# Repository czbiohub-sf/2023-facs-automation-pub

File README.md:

# FACSAutomation

## Introduction
This repository contains the Python application and custom **czfacsautomation** package that have been designed for automating the cell sorting on the Sony SH800S, by the CZ Biohub - SF Bioengineering team. All utilities support Python 3.7. Note that newer versions of Python are not compatible.

*This is a public snapshot of the FACS Automation repo as described in our 2023 preprint [here](https://www.biorxiv.org/content/10.1101/2023.03.24.534165v1).*

Maintenance of this repo is the responsibility of Diane Wiener. Please direct any communication to Diane Wiener via creation of an Issue at the project repo [here](https://github.com/czbiohub/2023-facs-automation-pub/issues).

This source describes Open Hardware, which is licensed under the CERN-OHL-W v2. 

Electronics hardware is described in the facs_electronics folder.

CAD designs are provided in Onshape [here](https://cad.onshape.com/documents/c1a3ab256e8df7a71b82db8c/w/ab65c37920d47d4a2484a277/e/421207c6e308bccf3dd4e5b1?configuration=default&renderMode=0&uiState=640b930bf24bcf207edf60a6).

Software is licensed under BSD 3-Clause.

Copyright Chan Zuckerberg Biohub - San Francisco 2023.

## Contents

### Classes
`czfacsautomation/hardware/`
* __`HardwareController`__ - Interfaces with hardware peripherals
* __`ZaberController`__ - Communicates with the zaber stages and gripper
* __`ArduinoController`__ - Communicates with the arduino via serial

`czfacsautomation/sorting/`
* __`Controller`__ - Creates wrapper classes for auto click methods used for interfacing with the Sony SH800S GUI
* __`Sort`__ - Runs a single sort on the Sony SH800S GUI
* __`Gating`__ - Runs the GateVertexTool to get and set gate on the Sony SH800S GUI
* __`CreateGate`__ - Creates a custom gate using the cell population data

`czfacsautomation/integration/`
* __`FACSAutomation`__ - Main class to call, starts process, and implements pause/stop

`czfacsautomation/slack/`
* __`SlackFacs`__ - Communicates with Slack App to notify users of current run status.

### Config Files
* __`config/hardware_config.json`__ - Holds the hardware configuration parameters for the zaber stages and arduino
* __`config/gui_config.json`__ - Holds the config file of all screenshots and parameters needed to run sorting
* __`config/Slack_config.json`__ - Holds the configuration parameters for the various messages to post

### Vendor Folder
The GateVertexTool `vendor/GateVertexTool.exe` is available from Sony Biotechnology.
Requests to access the GateVertexTool may be made to SONY Biotechnology [here](https://go.sonybiotechnology.com/gate-vertex.html).
Store the file in the `vendor/GateVertexTool/` folder.

## Installation and Use
### Installing Module
1. On Windows OS: Add GateVertexTool folder to "Path" environment variable (read release notes for more details)
2. Create and/or activate a virtual environment in a convenient location with Python3
3. Install and add pytesseract to path
4. Download / clone this repository
5. Navigate to the base of the repository
6. Install setuptools `pip install setuptools`
7. Install module `pip install -e .`
8. Create the folder for the exported gating data in the location specified in the "GATE_CSV_DIR" path in the `gui_config.json` 

### Updating Module from Repository
1. Pull changes from remote repository
2. Activate virtual environment with previous install
3. Navigate to the module directory
4. Update module `pip install -e . --upgrade`

### Using Module
1. cd to the `src` directory
2. `python -m czfacsautomation "<hardware_config location>" "-facs" ""`

#### Module Routines:
1. Chill Tube Housing:
   
   `python -m czfacsautomation "<hardware_config location>" "-chill" ""`

2. Run FACS Automation:
   
   `python -m czfacsautomation "<hardware_config location>" "-facs" ""`

3. Data Scraper:
   
   `python -m czfacsautomation "<hardware_config location>" "-scrape" ""`

4. Hardware Demo:
   
   `python -m czfacsautomation "<hardware_config location>" "-demo" ""`

5. Calibration:
   
   a. Calibration Update Scan:
      
   `python -m czfacsautomation "<hardware_config location>" "-calibrate" "-s"`
   
   b. Tube Calibration Check:
      
   `python -m czfacsautomation "<hardware_config location>" "-calibrate" "-t"`
   
   c. Full Calibration Routine (Scanning and with Tubes):
      
   `python -m czfacsautomation "<hardware_config location>" "-calibrate" "-f"`

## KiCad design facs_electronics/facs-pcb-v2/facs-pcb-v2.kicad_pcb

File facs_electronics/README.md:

# FACSAutomation
Python libraries for automating cell sorting with the Sony SH800S GUI.

# Serial Commands
All commands should be sent via Serial with a newline ending, `\n`, e.g. send `VALVE\n`.
Upon initialization, all 18 motors are initialized but turned off, and the valve is switched open.
| Command | Description |
|--|--|
| `VALVE` | Toggles solenoid valve on/off. Solenoid is normally closed but initialized open. |
|`READ_TEMP` | Upon calling, will average collected temperature readings from 6 sensors and return in a string 0,0,0,0,0,0 |
|`M,X` | Reads motor status, where X is the motor of interest (zero-indexed). Let X = -1 to return all motor statuses in the form 0,0,0,0,0,0,0,0,0,0,0,0,0,0,0,0,0,0.|
|`S,[X]` | Switches state of motors, where X can be a variable list of motor nums (zero-indexed); e.g., `S,[0,1,2,17]` to toggle motor # 0, 1, 2, and 17 or `S,[0]` to toggle just the first motor. Will return `[motor_num, old state, new state]`, e.g. `[5, 1, 0]` if turning off the 5th (0-indexed) motor.|
|`E,X` | Stops motors based on the encoder reading. The motor must be turned on using `S,[X]` before using the encoder. When the encoder successfully picks up a signal, it will return:<br>`Detected`<br> `[motor_num,1,0]`<br>If it is unsuccessful, it will return: <br>`Not detected`<br>`[motor_num,1,0]`|
|`P,X`| Changes PWM of motors to X, ranging from 0-255.|
| `ON`| Turns all 18 motors on and sets PWM to 150.
| `OFF`| Turns all motors off AND sets PWM to 0 (think low-power OFF). To turn back on, either use `P,X` to set PWM and then toggle motors with `S,[X]` to turn on motors; or, `ON` to set PWM to 150 and enable all 18 motors. |

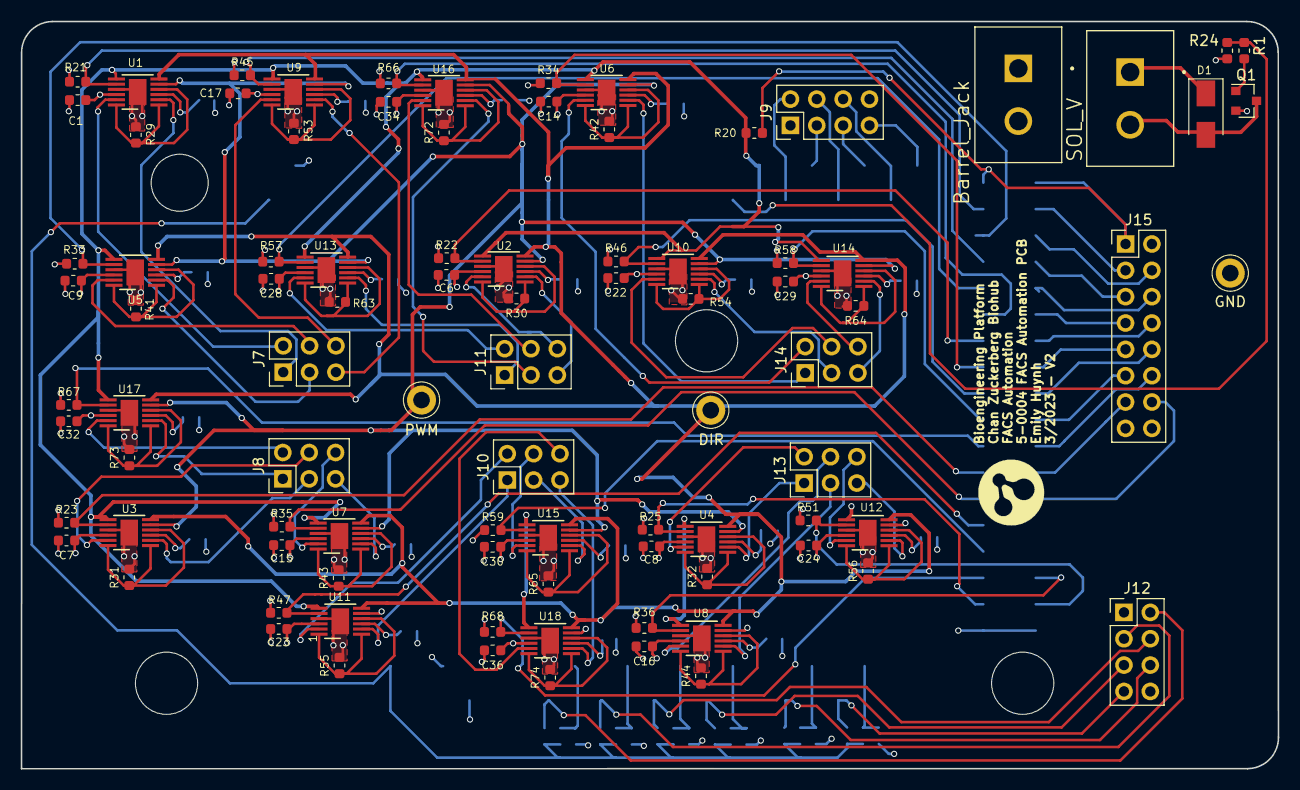
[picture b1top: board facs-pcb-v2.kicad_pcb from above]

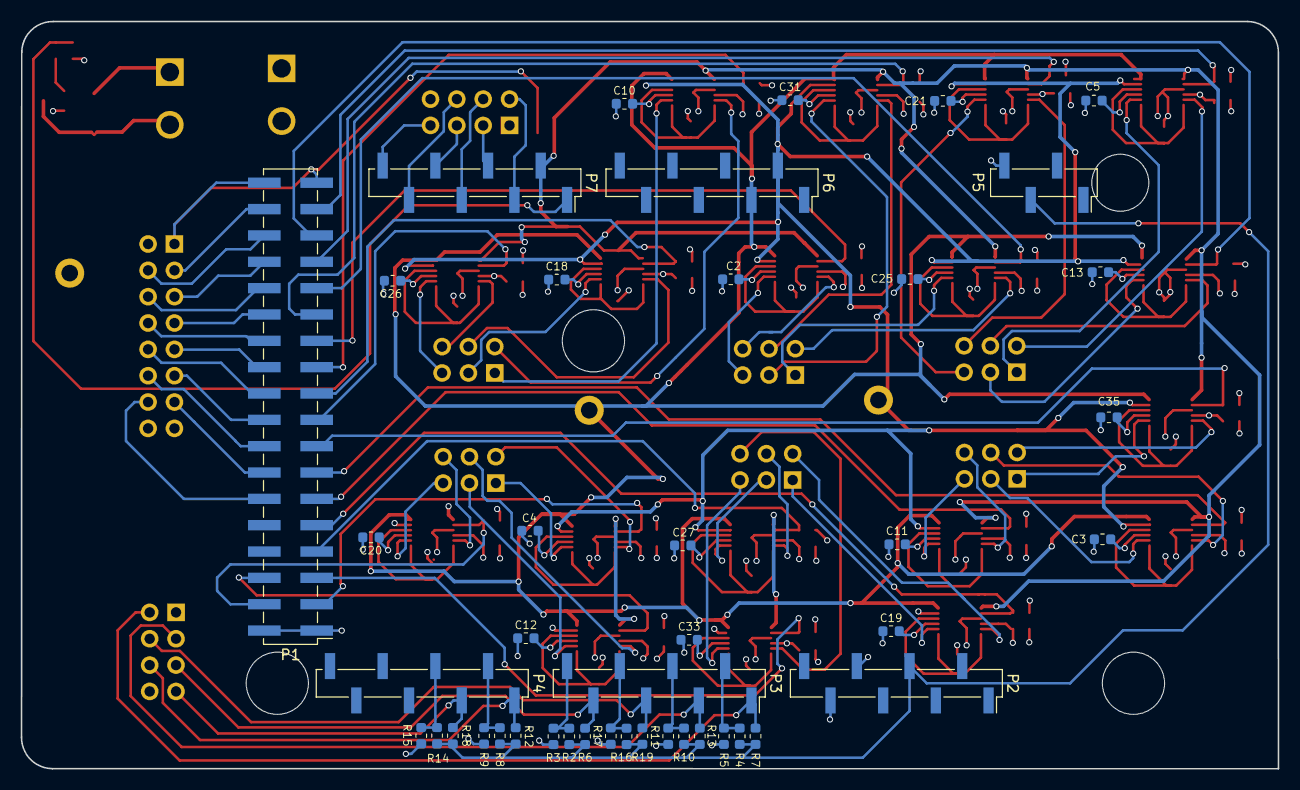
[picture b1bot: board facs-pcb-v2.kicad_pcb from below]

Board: 4 copper layers, 121.2 x 72.0 mm, 138 parts (43 on the bottom side), 112 nets.

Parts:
C1, C2, C3, C4, C9, C10, C11, C12, C17, C18, C19, C20, C25, C26, C27, C31, C32, C33: 10uF; C_0603_1608Metric
C5, C6, C7, C8, C13, C14, C15, C16, C21, C22, C23, C24, C28, C29, C30, C34, C35, C36: 0.1uF; C_0603_1608Metric
D1: US1A; D_SMA
J5: SOL_V; TE_350422-1
J6: Barrel_Jack; TE_350422-1
J7: DSUB25-1-1; PinHeader_2x03_P2.54mm_Vertical
J8: DSUB25-2-1; PinHeader_2x03_P2.54mm_Vertical
J9: DSUB25-1-4; PinHeader_2x04_P2.54mm_Vertical
J10: DSUB25-2-2; PinHeader_2x03_P2.54mm_Vertical
J11: DSUB25-1-2; PinHeader_2x03_P2.54mm_Vertical
J12: DSUB25-2-4; PinHeader_2x04_P2.54mm_Vertical
J13: DSUB25-2-3; PinHeader_2x03_P2.54mm_Vertical
J14: DSUB25-1-3; PinHeader_2x03_P2.54mm_Vertical
J15: DSUB15-1; PinHeader_2x08_P2.54mm_Vertical
P1: Digital; PinHeader_2x18_P2.54mm_Vertical_SMD
P2: Power; PinHeader_1x08_P2.54mm_Vertical_SMD_Pin1Right
P3, P4: Analog; PinHeader_1x08_P2.54mm_Vertical_SMD_Pin1Right
P5: PWM; PinHeader_1x04_P2.54mm_Vertical_SMD_Pin1Right
P6: PWM; PinHeader_1x08_P2.54mm_Vertical_SMD_Pin1Right
P7: Communication; PinHeader_1x08_P2.54mm_Vertical_SMD_Pin1Right
P8, P10, P12: CONN_01X01; MountingHole_6mm
P11: CONN_01X01; MountingHole_5.5mm
Q1: IRLML2060; SOT-23
R1: 330; R_0603_1608Metric
R2, R3, R4, R5, R6, R7, R8, R9, R10, R11, R12, R13, R14, R15, R16, R17, R18, R19, R20, R24: 10k; R_0603_1608Metric
R21, R22, R23, R25, R33, R34, R35, R36, R45, R46, R47, R51, R57, R58, R59, R66, R67, R68: 100k; R_0603_1608Metric
R29, R30, R31, R32, R41, R42, R43, R44, R53, R54, R55, R56, R63, R64, R65, R72, R73, R74: 500m; R_0603_1608Metric
TP1: DIR; TestPoint_Keystone_5005-5009_Compact
TP2: PWM; TestPoint_Keystone_5005-5009_Compact
TP3: GND; TestPoint_Keystone_5005-5009_Compact
U1, U2, U3, U4, U5, U6, U7, U8, U9, U10, U11, U12, U13, U14, U15, U16, U17, U18: MAX14870; DFN-12-1EP_3x3mm_P0.5mm_EP1.70x2.50mm

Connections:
+3V3: P2.4, P5.3, R2.1, R4.1, R6.1, R7.1, R8.1, R10.1, R12.1, R13.1, R14.1, R16.1, R18.1, R19.1
+5V: J15.1, P1.35, P1.36, R20.2
+12V: C1.1, C2.1, C3.1, C4.1, C5.1, C6.1, C7.1, C8.1, C9.1, C10.1, C11.1, C12.1, C13.1, C14.1, C15.1, C16.1, C17.1, C18.1, C19.1, C20.1, C21.1, C22.1, C23.1, C24.1, C25.1, C26.1, C27.1, C28.1, C29.1, C30.1, C31.1, C32.1, C33.1, C34.1, C35.1, C36.1, D1.1, J5.1, J6.1, U1.3, U1.10, U2.3, U2.10, U3.3, U3.10, U4.3, U4.10, U5.3, U5.10, U6.3, U6.10, U7.3, U7.10, U8.3, U8.10, U9.3, U9.10, U10.3, U10.10, U11.3, U11.10, U12.3, U12.10, U13.3, U13.10, U14.3, U14.10, U15.3, U15.10, U16.3, U16.10, U17.3, U17.10, U18.3, U18.10
/DIR: P6.3, TP1.1, U1.6, U2.6, U3.6, U4.6, U5.6, U6.6, U7.6, U8.6, U9.6, U10.6, U11.6, U12.6, U13.6, U14.6, U15.6, U16.6, U17.6, U18.6
/ENC_1: J9.2, P7.3
/ENC_2: J9.3, P7.4
/ENC_3: J9.4, P7.5
/ENC_4: J9.5, P7.6
/ENC_5: J9.6, P7.7
/ENC_6: J9.7, P7.8
/ENC_7: J15.3, P1.34
/ENC_8: J15.4, P1.32
/ENC_9: J15.5, P1.30
/ENC_10: J15.6, P1.28
/ENC_11: J15.7, P1.26
/ENC_12: J15.8, P1.24
/ENC_13: J15.9, P1.22
/ENC_14: J15.10, P1.20
/ENC_15: J15.11, P1.18
/ENC_16: J15.12, P1.16
/ENC_17: J15.13, P1.14
/ENC_18: J15.14, P1.12
/FAULT: P7.2, R20.1, U1.7, U2.7, U3.7, U4.7, U5.7, U6.7, U7.7, U8.7, U9.7, U10.7, U11.7, U12.7, U13.7, U14.7, U15.7, U16.7, U17.7, U18.7
/M1: P1.33, R21.1, U1.8
/M2: P1.31, R33.1, U5.8
/M3: P1.29, R45.1, U9.8
/M4: P1.27, R57.1, U13.8
/M5: P1.25, R66.1, U16.8
/M6: P1.23, R22.1, U2.8
/M7: P1.21, R34.1, U6.8
/M8: P1.19, R46.1, U10.8
/M9: P1.17, R58.1, U14.8
/M10: P1.15, R67.1, U17.8
/M11: P1.13, R23.1, U3.8
/M12: P1.11, R35.1, U7.8
/M13: P1.9, R47.1, U11.8
/M14: P1.7, R59.1, U15.8
/M15: P1.5, R68.1, U18.8
/M16: P1.3, R25.1, U4.8
/M17: P1.6, R36.1, U8.8
/M18: P1.4, R51.1, U12.8
/MA1: J7.1, U1.2
/MA2: J7.3, U5.2
/MA3: J7.5, U9.2
/MA4: J11.1, U13.2
/MA5: J11.3, U16.2
/MA6: J11.5, U2.2
/MA7: J14.1, U6.2
/MA8: J14.3, U10.2
/MA9: J14.5, U14.2
/MA10: J8.1, U17.2
/MA11: J8.3, U3.2
/MA12: J8.5, U7.2
/MA13: J10.1, U11.2
/MA14: J10.3, U15.2
/MA15: J10.5, U18.2
/MA16: J13.1, U4.2
/MA17: J13.3, U8.2
/MA18: J13.5, U12.2
/MB1: J7.2, U1.11
/MB2: J7.4, U5.11
/MB3: J7.6, U9.11
/MB4: J11.2, U13.11
/MB5: J11.4, U16.11
/MB6: J11.6, U2.11
/MB7: J14.2, U6.11
/MB8: J14.4, U10.11
/MB9: J14.6, U14.11
/MB10: J8.2, U17.11
/MB11: J8.4, U3.11
/MB12: J8.6, U7.11
/MB13: J10.2, U11.11
/MB14: J10.4, U15.11
/MB15: J10.6, U18.11
/MB16: J13.2, U4.11
/MB17: J13.4, U8.11
/MB18: J13.6, U12.11
/PWM: P6.2, TP2.1, U1.5, U2.5, U3.5, U4.5, U5.5, U6.5, U7.5, U8.5, U9.5, U10.5, U11.5, U12.5, U13.5, U14.5, U15.5, U16.5, U17.5, U18.5
/SOL_V: P7.1, R1.1, R24.1
/TEMP_1: J12.2, P3.1, R7.2
/TEMP_2: J12.3, P3.3, R13.2
/TEMP_3: J12.4, P3.5, R19.2
/TEMP_4: J12.5, P3.7, R6.2
/TEMP_5: J12.6, P4.1, R12.2
/TEMP_6: J12.7, P4.3, R18.2
/TEMP_D1: P3.2, R4.2, R5.1
/TEMP_D2: P3.4, R10.2, R11.1
/TEMP_D3: P3.6, R16.2, R17.1
/TEMP_D4: P3.8, R2.2, R3.1
/TEMP_D5: P4.2, R8.2, R9.1
/TEMP_D6: P4.4, R14.2, R15.1
GND: C1.2, C2.2, C3.2, C4.2, C5.2, C6.2, C7.2, C8.2, C9.2, C10.2, C11.2, C12.2, C13.2, C14.2, C15.2, C16.2, C17.2, C18.2, C19.2, C20.2, C21.2, C22.2, C23.2, C24.2, C25.2, C26.2, C27.2, C28.2, C29.2, C30.2, C31.2, C32.2, C33.2, C34.2, C35.2, C36.2, J6.2, J9.1, J12.1, J15.15, P1.1, P1.2, P2.6, P2.7, P5.4, Q1.2, R3.2, R5.2, R9.2, R11.2, R15.2, R17.2, R21.2, R22.2, R23.2, R24.2, R25.2, R29.2, R30.2, R31.2, R32.2, R33.2, R34.2, R35.2, R36.2, R41.2, R42.2, R43.2, R44.2, R45.2, R46.2, R47.2, R51.2, R53.2, R54.2, R55.2, R56.2, R57.2, R58.2, R59.2, R63.2, R64.2, R65.2, R66.2, R67.2, R68.2, R72.2, R73.2, R74.2, TP3.1, U1.9, U1.13, U2.9, U2.13, U3.9, U3.13, U4.9, U4.13, U5.9, U5.13, U6.9, U6.13, U7.9, U7.13, U8.9, U8.13, U9.9, U9.13, U10.9, U10.13, U11.9, U11.13, U12.9, U12.13, U13.9, U13.13, U14.9, U14.13, U15.9, U15.13, U16.9, U16.13, U17.9, U17.13, U18.9, U18.13
unnamed: D1.2, J5.2, Q1.3
unnamed: Q1.1, R1.2
unnamed: R29.1, U1.1, U1.4, U1.12
unnamed: R30.1, U2.1, U2.4, U2.12
unnamed: R31.1, U3.1, U3.4, U3.12
unnamed: R32.1, U4.1, U4.4, U4.12
unnamed: R41.1, U5.1, U5.4, U5.12
unnamed: R42.1, U6.1, U6.4, U6.12
unnamed: R43.1, U7.1, U7.4, U7.12
unnamed: R44.1, U8.1, U8.4, U8.12
unnamed: R53.1, U9.1, U9.4, U9.12
unnamed: R54.1, U10.1, U10.4, U10.12
unnamed: R55.1, U11.1, U11.4, U11.12
unnamed: R56.1, U12.1, U12.4, U12.12
unnamed: R63.1, U13.1, U13.4, U13.12
unnamed: R64.1, U14.1, U14.4, U14.12
unnamed: R65.1, U15.1, U15.4, U15.12
unnamed: R72.1, U16.1, U16.4, U16.12
unnamed: R73.1, U17.1, U17.4, U17.12
unnamed: R74.1, U18.1, U18.4, U18.12

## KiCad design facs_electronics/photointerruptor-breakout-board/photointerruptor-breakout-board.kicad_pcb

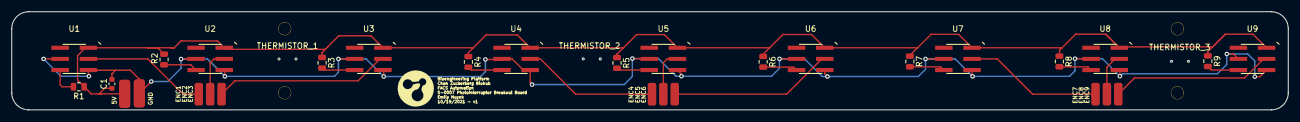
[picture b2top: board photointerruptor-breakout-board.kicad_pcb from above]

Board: 2 copper layers, 224.5 x 17.3 mm, 34 parts (0 on the bottom side), 20 nets.

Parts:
C1: 0.1 uF; C_0603_1608Metric
ENC1, ENC2, ENC3, ENC4, ENC5, ENC6, ENC7, ENC8, ENC9: MountingHole_Pad; power-pads_copy
H1, H2, H3, H4: MountingHole; MountingHole_2.3mm_#2
H5: 5V; power-pads
H6: GND; power-pads
R1, R2, R3, R4, R5, R6, R7, R8, R9: 220; R_0805_2012Metric
U1, U2, U3, U4, U5, U6, U7, U8, U9: AEDR-8300; Broadcom_DFN-6_2x2mm_P0.65mm

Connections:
+5V: C1.1, H5.1, R1.1, R2.1, R3.1, R4.1, R5.1, R6.1, R7.1, R8.1, R9.1, U1.6, U2.6, U3.6, U4.6, U5.6, U6.6, U7.6, U8.6, U9.6
/ENC_1: ENC1.1, U1.5
/ENC_2: ENC2.1, U2.5
/ENC_3: ENC3.1, U3.5
/ENC_4: ENC4.1, U4.5
/ENC_5: ENC5.1, U5.5
/ENC_6: ENC6.1, U6.5
/ENC_7: ENC7.1, U7.5
/ENC_8: ENC8.1, U8.5
/ENC_9: ENC9.1, U9.5
GND: C1.2, H6.1, U1.2, U1.4, U2.2, U2.4, U3.2, U3.4, U4.2, U4.4, U5.2, U5.4, U6.2, U6.4, U7.2, U7.4, U8.2, U8.4, U9.2, U9.4
unnamed: R1.2, U1.3
unnamed: R2.2, U2.3
unnamed: R3.2, U3.3
unnamed: R4.2, U4.3
unnamed: R5.2, U5.3
unnamed: R6.2, U6.3
unnamed: R7.2, U7.3
unnamed: R8.2, U8.3
unnamed: R9.2, U9.3

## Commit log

2023-03-17 Start upload for snapshot of facs-automation repo
    Partial upload of facs-automation repo snapshot of commit c8857e558fd9b56f15f0afa67903b626fc21924b.
2023-03-17 Continue upload snapshot of facs-automation repo
    Additional files in facs-automation repo snapshot of c8857e558fd9b56f15f0afa67903b626fc21924b
2023-03-17 Create .gitignore
    Snapshot from facs-automation commit c8857e558fd9b56f15f0afa67903b626fc21924b
2023-03-17 Minor edits to README.md
2023-03-24 CZ Biohub SF
    Affiliation change to CZ Biohub SF.
2023-03-27 Add bioRxiv link
2023-03-27 Update README.md
    typo fix
2023-03-27 Slack & filepath location
    -Hotfix for Slack after they updated their certificates
    -Filepaths updated after new setup and install for updated repo
2023-03-28 Updated the affiliation
2023-03-28 Updated the affiliation (#6)
2023-05-24 Delete facs_automation.py
    Delete outdated facs_automation.py code in prep for uploading new file
2023-05-24 Upload latest facs_automation.py file
    Revision to facs_automation.py for slack connection errors and hotfix for keyboard listener
2023-05-24 slack.py update
    Update to slack.py if it is not possible to connect to slack
